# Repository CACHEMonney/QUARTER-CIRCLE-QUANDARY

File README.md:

# QUARTER-CIRCLE-QUANDARY
Have you ever wanted perfect motion inputs?

Do you want to make programming even easier?

Well do I have the project form you, the quarter circle quandary hopes to take you from wasting away in pools to being Daigo. A project that can be used for editing shortcuts and programming using the ergonomics of a hitbox adapting for left-handedness to suit all your fighting game needs as well as being useful in daily computer activity with multiple layers of inputs for different usages.

By smashing all keys you should be able to switche between WORK and PLAY

WORK HARD:
  1. Design commands for editing music and modelling
  2. Code shortcut for shortening long word 

WORK PLAY:
  1. Arrow key based control scheme
  2. WASD based control scheme

PAD

PCB

FRAME

BOM:

XIAO RP2040 (1) *https://www.aliexpress.com/item/1005003682505451.html?spm=a2g0o.cart.0.0.6eaf38da3X1JOq&mp=1

SK6812 MINI-E LEDs (2) *https://www.aliexpress.com/item/1005007863635868.html?spm=a2g0o.cart.0.0.6eaf38da3X1JOq&mp=1

MX-Style switches (10) *https://www.aliexpress.com/item/1005002971598717.html?spm=a2g0o.cart.0.0.6eaf38da3X1JOq&mp=1

M3x16mm screws (4) *https://www.aliexpress.com/w/wholesale-M3x16mm-screws.html?spm=a2g0o.detail.search.0

  Subtotal $20.48

PCB *https://jlcpcb.com/

  Subtotal $18.83

Case print (top and bottom) *done by my friend

Total $39.31

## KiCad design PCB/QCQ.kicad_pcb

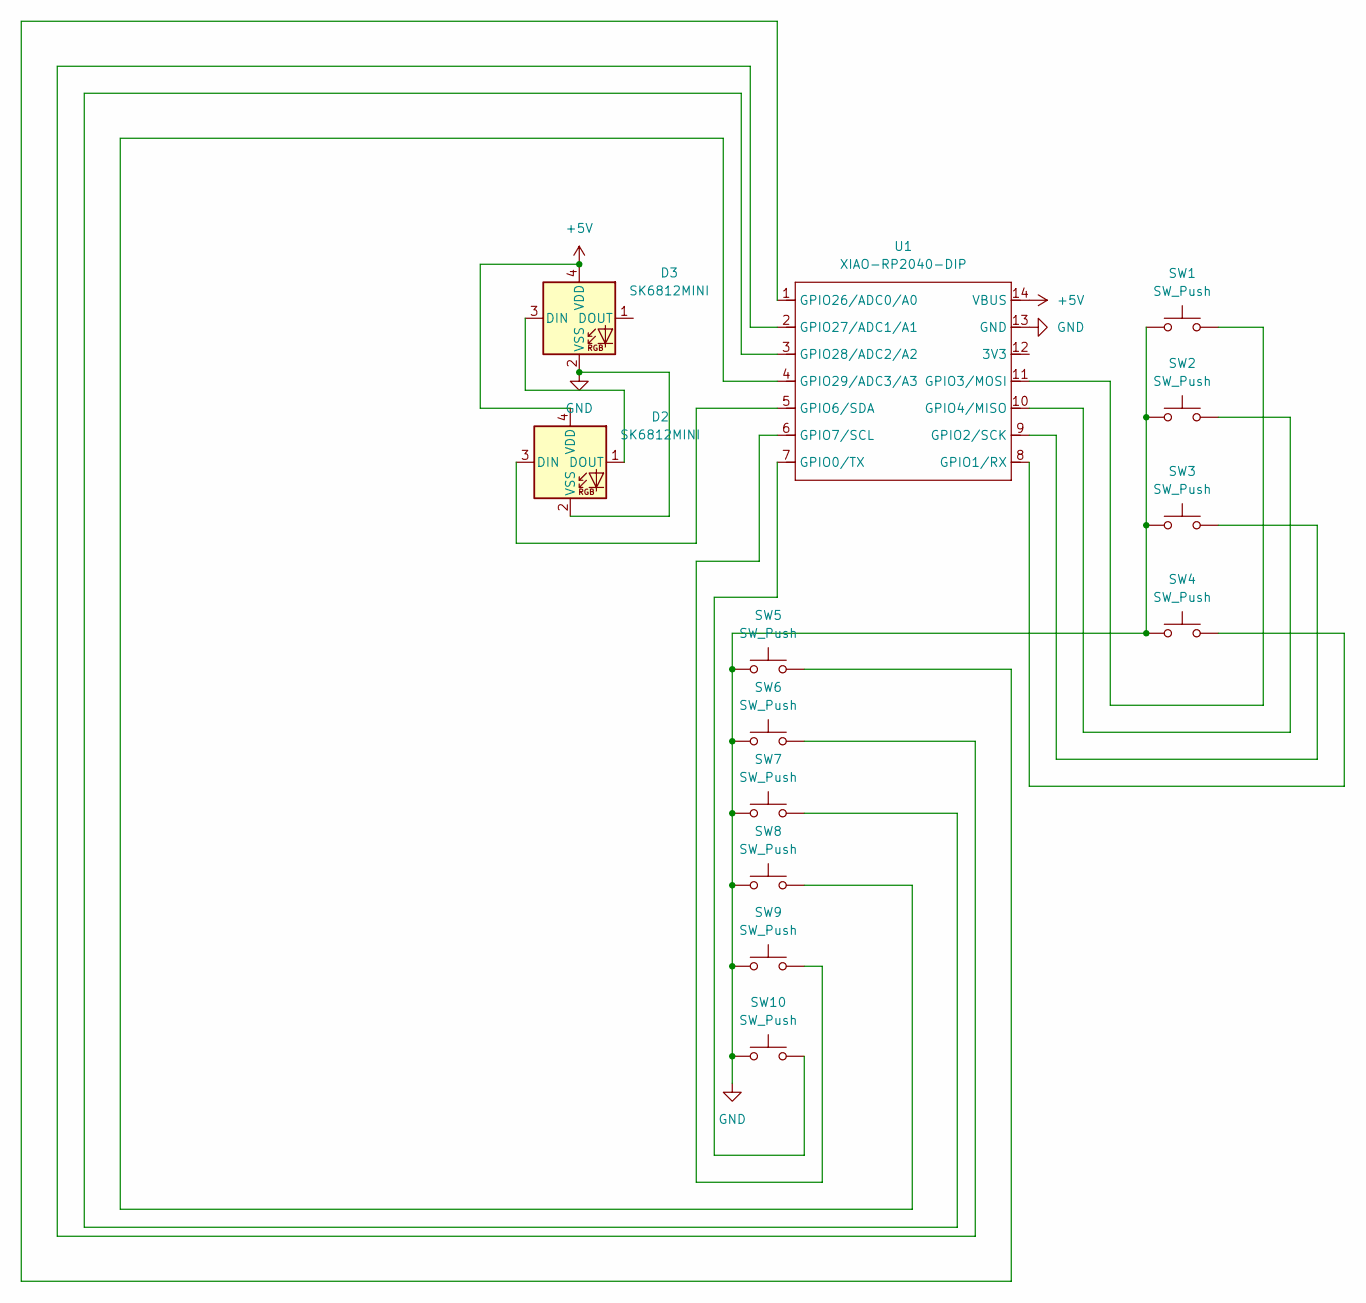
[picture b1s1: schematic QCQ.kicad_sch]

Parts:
D2, D3: SK6812MINI; LED_SK6812MINI_PLCC4_3.5x3.5mm_P1.75mm
SW1, SW2, SW3, SW4, SW5, SW6, SW7, SW8, SW9, SW10: SW_Push; SW_Cherry_MX_1.00u_PCB
U1: XIAO-RP2040-DIP

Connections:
+5V: D2.4 (VDD), D3.4 (VDD), U1.14 (VBUS)
GND: D2.2 (VSS), D3.2 (VSS), SW1.1, SW2.1, SW3.1, SW4.1, SW5.1, SW6.1, SW7.1, SW8.1, SW9.1, SW10.1, U1.13 (GND)
unnamed: D2.3 (DIN), U1.5 (GPIO6/SDA)
unnamed: D2.1 (DOUT), D3.3 (DIN)
unnamed: SW10.2, U1.7 (GPIO0/TX)
unnamed: SW4.2, U1.8 (GPIO1/RX)
unnamed: SW3.2, U1.9 (GPIO2/SCK)
unnamed: SW1.2, U1.11 (GPIO3/MOSI)
unnamed: SW2.2, U1.10 (GPIO4/MISO)
unnamed: SW9.2, U1.6 (GPIO7/SCL)
unnamed: SW5.2, U1.1 (GPIO26/ADC0/A0)
unnamed: SW6.2, U1.2 (GPIO27/ADC1/A1)
unnamed: SW7.2, U1.3 (GPIO28/ADC2/A2)
unnamed: SW8.2, U1.4 (GPIO29/ADC3/A3)

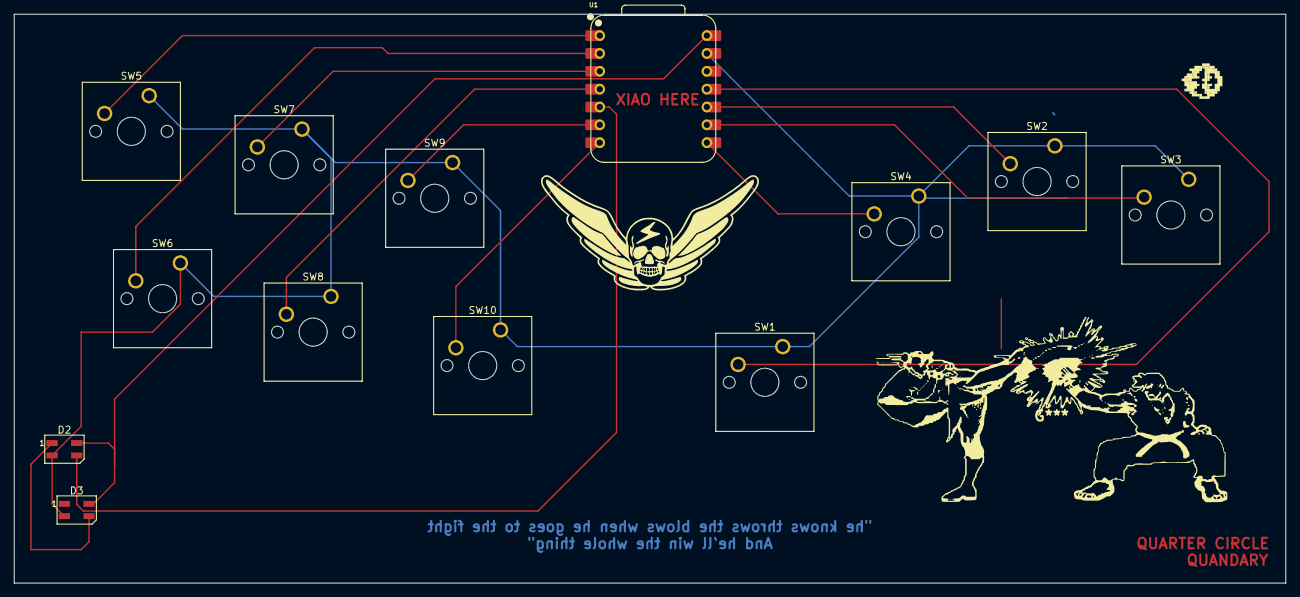
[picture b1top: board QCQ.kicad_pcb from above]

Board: 2 copper layers, 181.0 x 81.0 mm, 13 parts (0 on the bottom side), 14 nets.
